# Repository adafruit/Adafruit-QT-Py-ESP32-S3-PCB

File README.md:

## Adafruit QT Py ESP32-S3 WiFi Dev Board PCB

<a href="http://www.adafruit.com/products/5426"><br/>
Click here to purchase one from the Adafruit shop</a>

PCB files for the Adafruit QT Py ESP32-S3 WiFi Dev Board. 

Format is EagleCAD schematic and board layout
* https://www.adafruit.com/product/5426

### Description

The ESP32-S3 has arrived in QT Py format - and what a great way to get started with this powerful new chip from Espressif! With dual 240 MHz cores, WiFi and BLE support, and native USB, this QT Py is great for powering your IoT projects.

The ESP32-S3 is a highly-integrated, low-power, 2.4 GHz Wi-Fi System-on-Chip (SoC) solution that now has WiFi and BLE support, built-in native USB as well as some other interesting new technologies like Time of Flight distance measurements. With its state-of-the-art power and RF performance, this SoC is an ideal choice for a wide variety of application scenarios relating to the Internet of Things (IoT), wearable electronics, and smart homes. 

With native USB and 8 MB Flash this board will let you upgrade your existing ESP32 projects. Native USB means it can act like a keyboard or a disk drive, and no external USB-to-Serial converter required. WiFi and BLE mean it's awesome for IoT projects.

OLEDs! Inertial Measurement Units! Sensors a-plenty. All plug-and-play thanks to the innovative chainable design: SparkFun Qwiic-compatible STEMMA QT connectors for the I2C bus so you don't even need to solder! Just plug in a compatible cable and attach it to your MCU of choice, and you’re ready to load up some software and measure some light. Seeed Grove I2C boards will also work with this adapter cable.

Pinout and shape are Seeed Xiao compatible, with castellated pads so you can solder it flat to a PCB. In addition to the QT connector, we also added an RGB NeoPixel (with controllable power pin to allow for ultra-low-power usage), a reset button (great for restarting your program or entering the bootloader), and a button on GPIO 0 for entering the ROM bootloader or for user input

The ESP32-S3 has a dual-core 240 MHz chip, so it is comparable to ESP32's dual-core. However, there is no Bluetooth Classic support, only Bluetooth LE. This chip is a great step up from the earlier ESP32-S2! This ESP32-S3 chip we are using on the QT Py comes with 8 MB flash and no PSRAM, but it does have 512KB of SRAM so its fine for use with CircuitPython support as long as massive buffers are not needed. It's also great for use in ESP-IDF or with Arduino support.

* Same size, form-factor, and pin-out as Seeed Xiao
* USB Type C connector - If you have only Micro B cables, this adapter will come in handy!
* ESP32-S3 Dual Core 240MHz Tensilica processor - the next generation of ESP32-Sx, with native USB so it can act like a keyboard/mouse, MIDI device, disk drive, etc!
* Comes with 8MB Flash, 512KB SRAM, no PSRAM
* Native USB supported by every OS - can be used in Arduino or CircuitPython as USB serial console, MIDI, Keyboard/Mouse HID, even a little disk drive for storing Python scripts.
* Can be used with Arduino IDE or CircuitPython
* Built-in RGB NeoPixel LED with power control to reduce quiescent power in deep sleep
* Battery input pads on underside with diode protection for external battery packs up to 6V input
* 13 GPIO pins:
    * 11 on breakout pads, 2 more on QT connector
    * 10 x 12-bit analog inputs (SPI high speed pads do not have analog inputs)
    * PWM outputs on any pin
    * Two I2C ports, one on the breakout pads, and another with STEMMA QT plug-n-play connector
    * Hardware UART
    * Hardware SPI on the high speed SPI peripheral pins
    * Hardware I2S on any pins
    * 5 x Capacitive Touch with no additional components required
* 3.3V regulator with 600mA peak output
* Light sleep at 2~4mA, deep sleep at ~70uA
* Reset switch for starting your project code over, boot 0 button for entering bootloader mode
* Really really small

### License

Adafruit invests time and resources providing this open source design, please support Adafruit and open-source hardware by purchasing products from [Adafruit](https://www.adafruit.com)!

Designed by Limor Fried/Ladyada for Adafruit Industries.

Creative Commons Attribution/Share-Alike, all text above must be included in any redistribution. 
See license.txt for additional details.

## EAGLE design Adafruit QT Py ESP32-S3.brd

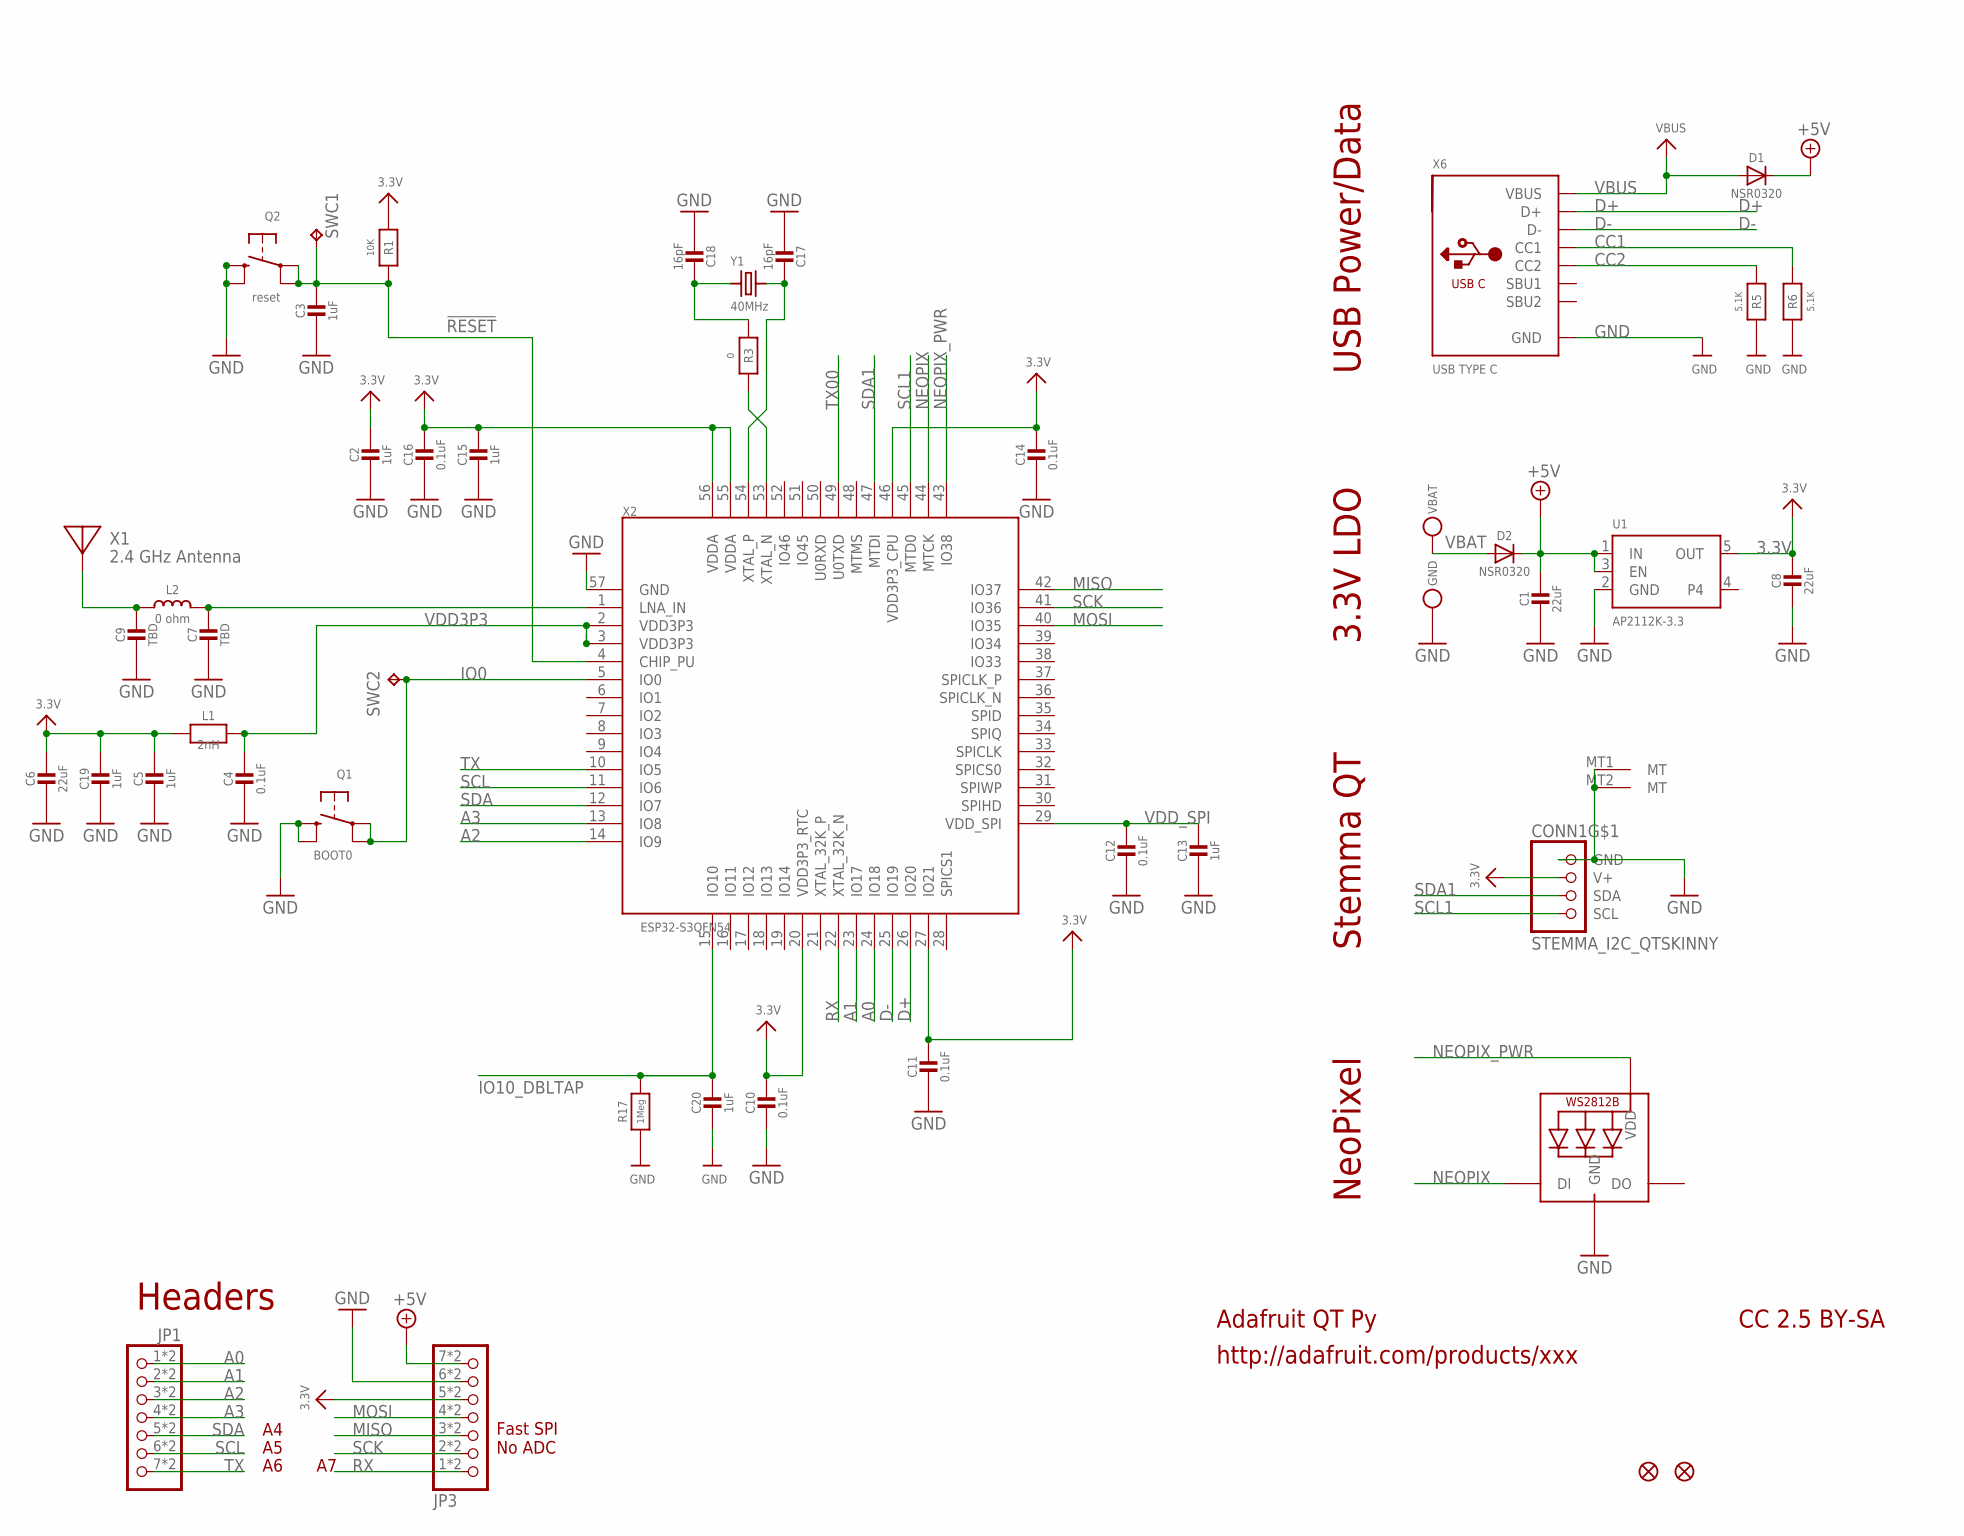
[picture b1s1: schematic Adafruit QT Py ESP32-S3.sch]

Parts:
C1, C6, C8: 22uF; 0805-NO
C2, C3, C5, C13, C15, C19, C20: 1uF; _0402NO
C4, C10, C11, C12, C14, C16: 0.1uF; _0402NO
C7, C9: TBD; _0402NO
C17, C18: 16pF; _0402NO
CONN1: STEMMA_I2C_QTSKINNY; JST_SH4_SKINNY
D1, D2: NSR0320; SOD-323_MINI
GND: TESTPOINT_MINUS; TESTPOINT_MINUS_1X3MM
JP1, JP3: HEADER-1X7_CASTEL; 1X07_CASTEL
L1: 2nH; _0402NO
L2: 0 ohm; _0402
LED1: WS2812B_SK6805_1515; SK6805_1515
Q1: BOOT0; BTN_KMR2_4.6X2.8
Q2: reset; BTN_KMR2_4.6X2.8
R1: 10K; _0402NO
R3: 0; _0402NO
R5, R6: 5.1K; _0402NO
R17: 1Meg; _0402NO
SWC1, SWC2: TPB1,27; B1,27
U1: AP2112K-3.3; SOT23-5
U$6, U$8: FIDUCIAL_1MM
VBAT: TESTPOINT_PLUS13; TESTPOINT_PLUS_1X3MM
X1: 2.4 GHz Antenna; ANT_2450AT18B100
X2: ESP32-S3QFN54; QFN56_7X7
X6: USB TYPE C; USB_C_CUSB31-CFM2AX-01-X
Y1: 40MHz; CRYSTAL_2X1.6

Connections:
3.3V: C2.1, C5.1, C6.1, C8.1, C10.1, C11.1, C14.1, C15.1, C16.1, C19.1, CONN1.2 (V+), JP3.5, JP3.5C (5), L1.1, R1.1, U1.5 (OUT), X2.20 (VDD3P3_RTC), X2.27 (IO21), X2.46 (VDD3P3_CPU), X2.55 (VDDA), X2.56 (VDDA)
!RESET: C3.1, Q2.A, Q2.A' (P1), R1.2, SWC1.TP, X2.4 (CHIP_PU)
+5V: C1.1, D1.C, D2.C, JP3.7, JP3.7C (7), U1.1 (IN), U1.3 (EN)
A0: JP1.1, JP1.1C (1), X2.24 (IO18)
A1: JP1.2, JP1.2C (2), X2.23 (IO17)
A2: JP1.3, JP1.3C (3), X2.14 (IO9)
A3: JP1.4, JP1.4C (4), X2.13 (IO8)
CC1: R6.2, X6.A5 (CC1)
CC2: R5.2, X6.B5 (CC2)
D+: X2.26 (IO20), X6.A6 (D+), X6.B6 (D+)
D-: X2.25 (IO19), X6.A7 (D-), X6.B7 (D-)
GND: C1.2, C2.2, C3.2, C4.2, C5.2, C6.2, C7.2, C8.2, C9.2, C10.2, C11.2, C12.2, C13.2, C14.2, C15.2, C16.2, C17.2, C18.2, C19.2, C20.2, CONN1.1 (GND), CONN1.MT1 (MT), CONN1.MT2 (MT), GND.P$1, JP3.6, JP3.6C (6), LED1.4 (GND), Q1.B (S), Q1.B' (S1), Q2.B (S), Q2.B' (S1), R5.1, R6.1, R17.1, U1.2 (GND), X2.57 (GND), X6.A1B12 (GND), X6.B1A12 (GND)
IO0: Q1.A, Q1.A' (P1), SWC2.TP, X2.5 (IO0)
IO10_DBLTAP: C20.1, R17.2, X2.15 (IO10)
MISO: JP3.3, JP3.3C (3), X2.42 (IO37)
MOSI: JP3.4, JP3.4C (4), X2.40 (IO35)
unnamed: R3.2, X2.53 (XTAL_N)
unnamed: C7.1, L2.2, X2.1 (LNA_IN)
unnamed: C9.1, L2.1, X1.FP
unnamed: C17.1, X2.54 (XTAL_P), Y1.3 (2)
unnamed: C18.1, R3.1, Y1.1
NEOPIX: LED1.1 (DI), X2.44 (MTCK)
NEOPIX_PWR: LED1.2 (VDD), X2.43 (IO38)
RX: JP3.1, JP3.1C (1), X2.22 (XTAL_32K_N)
SCK: JP3.2, JP3.2C (2), X2.41 (IO36)
SCL: JP1.6, JP1.6C (6), X2.11 (IO6)
SCL1: CONN1.4 (SCL), X2.45 (MTD0)
SDA: JP1.5, JP1.5C (5), X2.12 (IO7)
SDA1: CONN1.3 (SDA), X2.47 (MTDI)
TX: JP1.7, JP1.7C (7), X2.10 (IO5)
TX00: X2.49 (U0TXD)
VBAT: D2.A, VBAT.P$1
VBUS: D1.A, X6.A4B9 (VBUS), X6.B4A9 (VBUS)
VDD3P3: C4.1, L1.2, X2.2 (VDD3P3), X2.3 (VDD3P3)
VDD_SPI: C12.1, C13.1, X2.29 (VDD_SPI)

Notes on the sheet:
Adafruit QT Py
http://adafruit.com/products/xxx
CC 2.5 BY-SA
NeoPixel
Stemma QT
3.3V LDO
USB Power/Data
Headers
Fast SPI No ADC

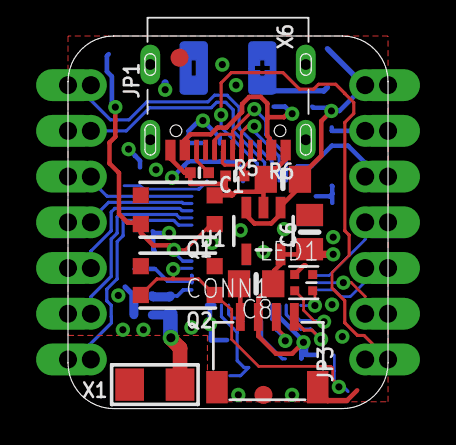
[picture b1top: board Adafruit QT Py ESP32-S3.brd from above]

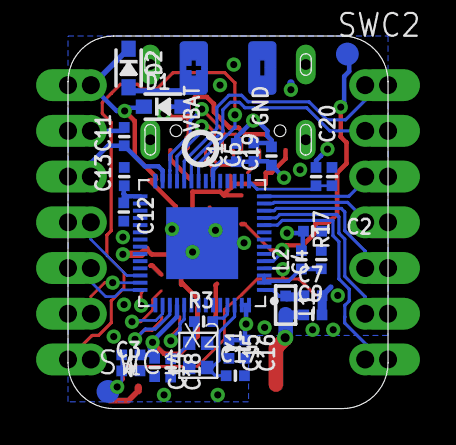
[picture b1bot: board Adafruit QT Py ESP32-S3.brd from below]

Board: 4 copper layers, 17.8 x 20.7 mm, 49 parts (32 on the bottom side), 34 nets.

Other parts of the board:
U$7: QTPY_ESP32_TOP
U$11: QTPYS3_BOT
U$12: PCBFEAT-REV-040

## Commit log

2022-06-14 adding prettypins
2022-06-24 adding reset
    adding reset file
2023-07-11 Updating factory reset
    Updating factory resets for PSRAM and No PSRAM variants
2023-07-19 updating bin files

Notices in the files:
parts and their libraries:
microbuilder: This work is placed in the public domain, and may be freely used for commercial and non-commercial work with the following conditions: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
